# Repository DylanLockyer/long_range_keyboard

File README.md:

# long_range_keyboard
Creating a wireless keyboard with a range of 10km.

\*\*\* Not yet finished\*\*\*

The goal is to create a module which can be used for two purposes. One module can be connected over USB to a keyboard which will provide input to an STM32. The other circuit will be connected to a computer (in this case an Nvidia Jetson Nano) over usb. The STM32 on the second board will emulate an HID keyboard, and will relay the keystrokes from the keyboard which will be sent between the devices over LORA wireless communication. The board is in the PCB layout stage.

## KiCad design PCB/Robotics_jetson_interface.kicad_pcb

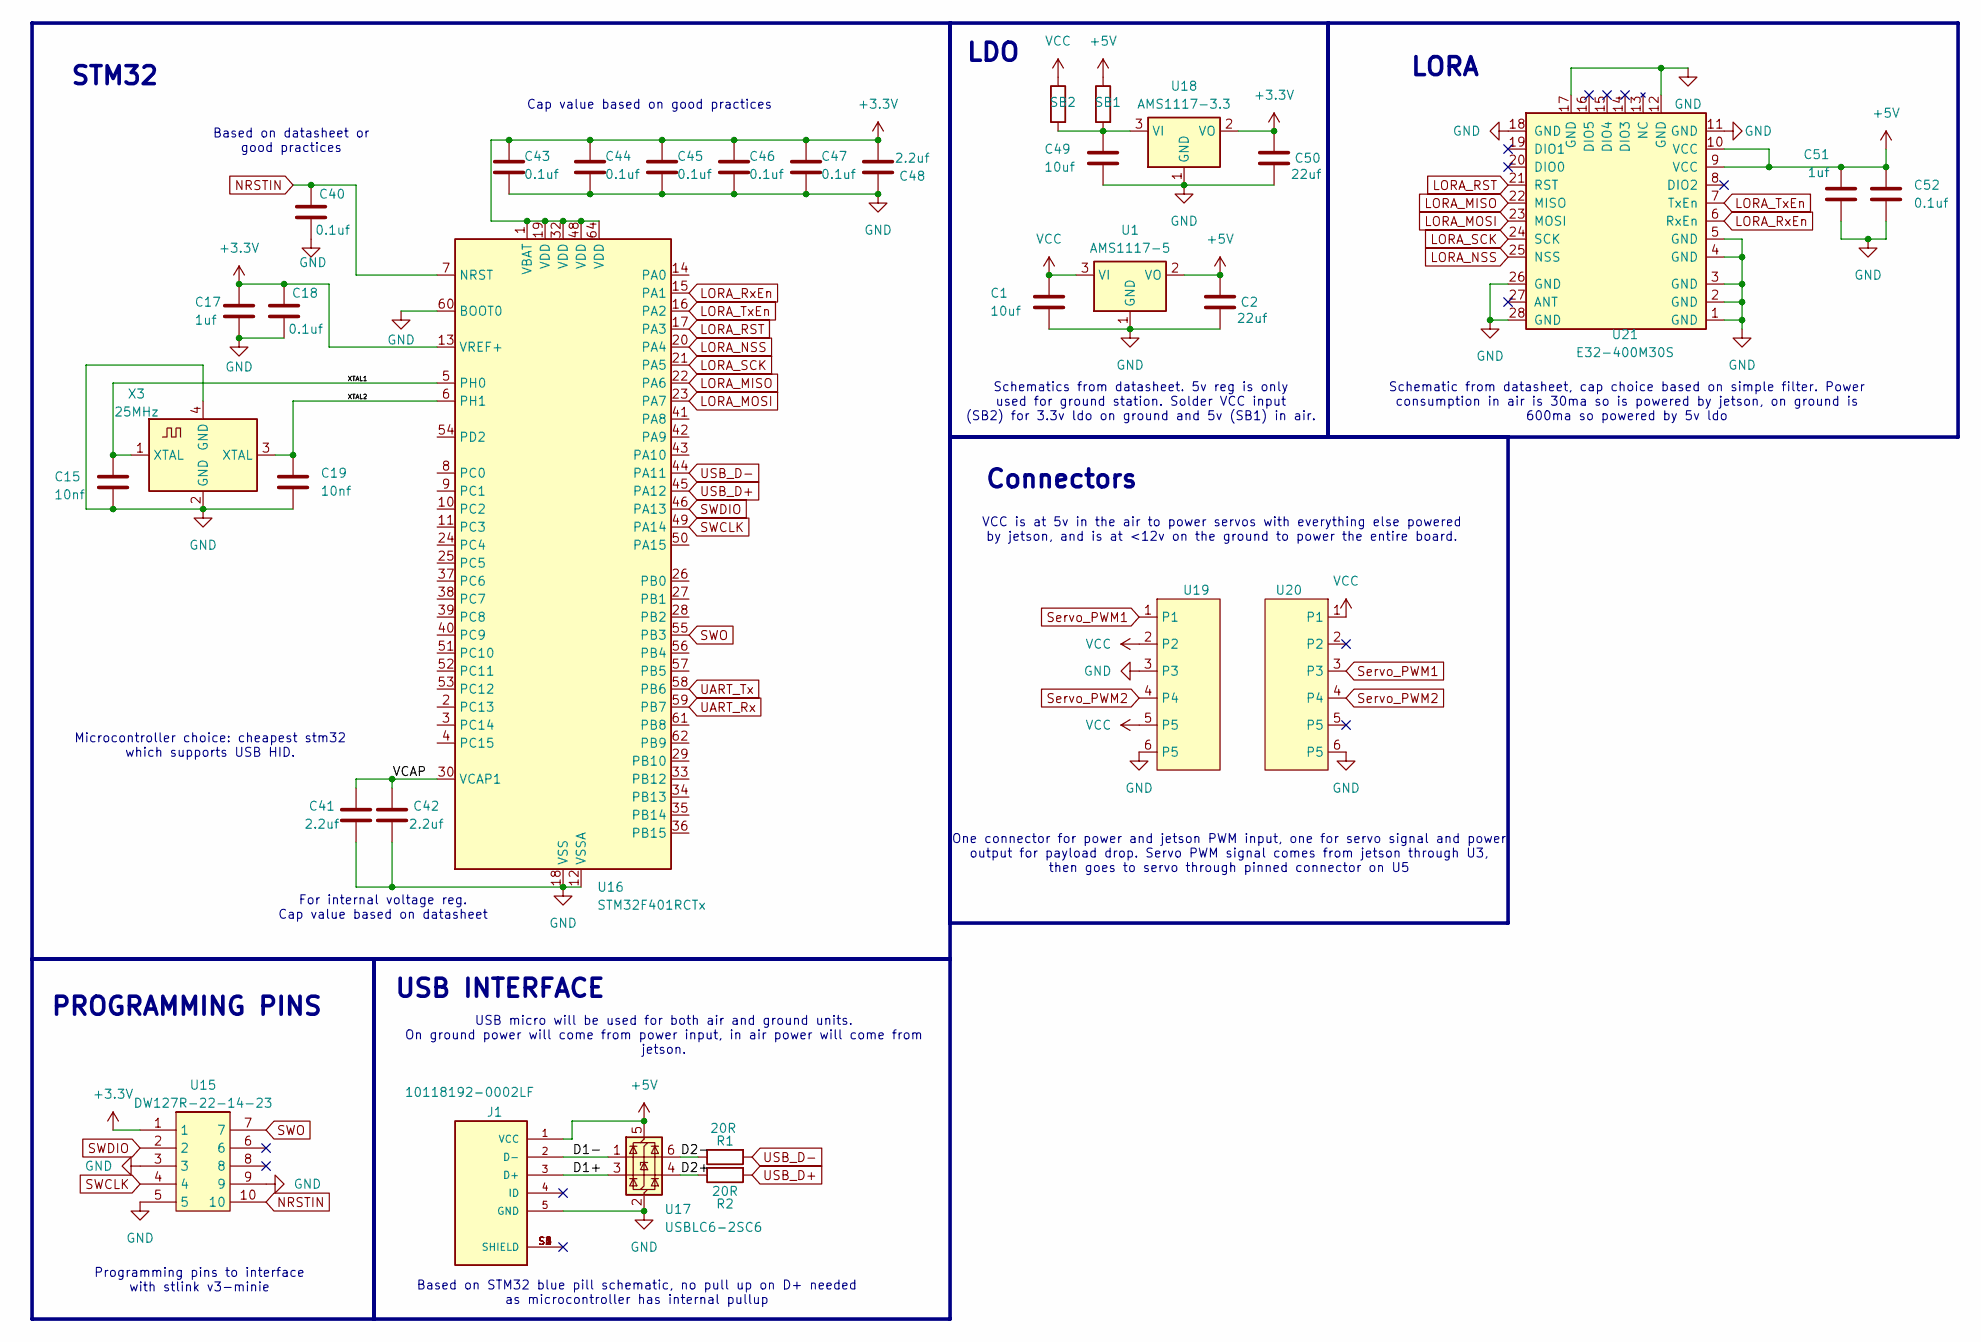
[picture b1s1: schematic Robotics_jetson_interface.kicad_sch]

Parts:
C1, C49: 10uf; C_0805_2012Metric
C2, C50: 22uf; C_0805_2012Metric_Pad1.18x1.45mm_HandSolder
C15, C19: 10nf; C_0805_2012Metric
C17, C51: 1uf; C_0603_1608Metric
C18, C40, C43, C44, C45, C46, C47, C52: 0.1uf; C_0402_1005Metric
C41, C42, C48: 2.2uf; C_0402_1005Metric
J1: 10118192-0002LF; AMPHENOL_10118192-0002LF; PARTREV B
R1, R2: 20R; R_0603_1608Metric
SB1, SB2: C_0603_1608Metric
U1: AMS1117-5; SOT-223-3_TabPin2
U15: DW127R-22-14-23
U16: STM32F401RCTx; LQFP-64_10x10mm_P0.5mm
U17: USBLC6-2SC6; SOT-23-6
U18: AMS1117-3.3; SOT-223-3_TabPin2
U19, U20: B06B-XASK-1-A
U21: E32-400M30S; E22-900M30S; PARTREV 1.4
X3: 25MHz; Crystal_SMD_3225-4Pin_3.2x2.5mm

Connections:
+3.3V: C17.1, C18.2, C43.1, C44.1, C45.1, C46.1, C47.1, C48.1, C50.1, U15.1, U16.1 (VBAT), U16.13 (VREF+), U16.19 (VDD), U16.32 (VDD), U16.48 (VDD), U16.64 (VDD), U18.2 (VO)
+5V: C2.1, C51.1, C52.1, J1.1 (VCC), SB1.1, U1.2 (VO), U17.5 (VBUS), U21.9 (VCC), U21.10 (VCC)
/D1+: J1.3 (D+), U17.3 (I/O2)
/D1-: J1.2 (D-), U17.1 (I/O1)
/D2+: R2.1, U17.4 (I/O2)
/D2-: R1.1, U17.6 (I/O1)
/VCAP: C41.2, C42.2, U16.30 (VCAP1)
/XTAL1: C15.1, U16.5 (PH0), X3.1 (XTAL)
/XTAL2: C19.1, U16.6 (PH1), X3.3 (XTAL)
GND: C1.2, C2.2, C15.2, C17.2, C18.1, C19.2, C40.1, C41.1, C42.1, C43.2, C44.2, C45.2, C46.2, C47.2, C48.2, C49.2, C50.2, C51.2, C52.2, J1.5 (GND), U1.1 (GND), U15.3, U15.5, U15.9, U16.12 (VSSA), U16.18 (VSS), U16.31 (VSS), U16.47 (VSS), U16.60 (BOOT0), U16.63 (VSS), U17.2 (GND), U18.1 (GND), U19.3, U19.6 (P5), U20.6 (P5), U21.1 (GND), U21.2 (GND), U21.3 (GND), U21.4 (GND), U21.5 (GND), U21.11 (GND), U21.12 (GND), U21.17 (GND), U21.18 (GND), U21.26 (GND), U21.28 (GND), X3.2 (GND), X3.4 (GND)
LORA_MISO: U16.22 (PA6), U21.22 (MISO)
LORA_MOSI: U16.23 (PA7), U21.23 (MOSI)
LORA_NSS: U16.20 (PA4), U21.25 (NSS)
LORA_RST: U16.17 (PA3), U21.21 (RST)
LORA_RxEn: U16.15 (PA1), U21.6 (RxEn)
LORA_SCK: U16.21 (PA5), U21.24 (SCK)
LORA_TxEn: U16.16 (PA2), U21.7 (TxEn)
NRSTIN: C40.2, U15.10, U16.7 (NRST)
unnamed: C49.1, SB1.2, SB2.2, U18.3 (VI)
SWCLK: U15.4, U16.49 (PA14)
SWDIO: U15.2, U16.46 (PA13)
SWO: U15.7, U16.55 (PB3)
Servo_PWM1: U19.1, U20.3
Servo_PWM2: U19.4, U20.4
UART_Rx: U16.59 (PB7)
UART_Tx: U16.58 (PB6)
USB_D+: R2.2, U16.45 (PA12)
USB_D-: R1.2, U16.44 (PA11)
VCC: C1.1, SB2.1, U1.3 (VI), U19.2, U19.5, U20.1

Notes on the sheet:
USB INTERFACE
Schematic from datasheet, cap choice based on simple filter. Power consumption in air is 30ma so is powered by jetson, on ground is 600ma so powered by 5v ldo
PROGRAMMING PINS
LORA
Schematics from datasheet. 5v reg is only used for ground station. Solder VCC input (SB2) for 3.3v ldo on ground and 5v (SB1) in air.
Based on datasheet or good practices
Based on STM32 blue pill schematic, no pull up on D+ needed as microcontroller has internal pullup
VCC is at 5v in the air to power servos with everything else powered by jetson, and is at <12v on the ground to power the entire board.
STM32
Microcontroller choice: cheapest stm32 which supports USB HID.
Connectors
For internal voltage reg. Cap value based on datasheet
One connector for power and jetson PWM input, one for servo signal and power output for payload drop. Servo PWM signal comes from jetson through U3, then goes to servo through pinned connector on U5
Cap value based on good practices
LDO
USB micro will be used for both air and ground units. On ground power will come from power input, in air power will come from jetson.
Programming pins to interface with stlink v3-minie

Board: 2 copper layers, 33 parts (22 on the bottom side), 27 nets, no tracks yet.

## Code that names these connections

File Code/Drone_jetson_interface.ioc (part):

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Mcu.Name=STM32F401R(B-C)Tx
Mcu.Package=LQFP64
Mcu.UserName=STM32F401RCTx
PA1.GPIOParameters=GPIO_Label
PA1.GPIO_Label=LORA_RxEn
PA1.Signal=GPIO_Output
PA10.Mode=OTG/Dual_Role_Device
PA10.Signal=USB_OTG_FS_ID
PA11.Mode=OTG/Dual_Role_Device
PA11.Signal=USB_OTG_FS_DM
PA12.Mode=OTG/Dual_Role_Device
PA12.Signal=USB_OTG_FS_DP
PA13.Mode=Trace_Asynchronous_SW
PA13.Signal=SYS_JTMS-SWDIO
PA14.Mode=Trace_Asynchronous_SW
PA14.Signal=SYS_JTCK-SWCLK
PA2.GPIOParameters=GPIO_Label
PA2.GPIO_Label=LORA_TxEn
PA2.Signal=GPIO_Output
PA3.GPIOParameters=GPIO_Label
PA3.GPIO_Label=LORA_RST
PA3.Signal=GPIO_Output
PA4.Mode=NSS_Signal_Hard_Output
PA4.Signal=SPI1_NSS
PA5.Mode=Full_Duplex_Master
PA5.Signal=SPI1_SCK
PA6.Mode=Full_Duplex_Master
PA6.Signal=SPI1_MISO
PA7.Mode=Full_Duplex_Master
PA7.Signal=SPI1_MOSI
PA9.Mode=Activate_VBUS
PA9.Signal=USB_OTG_FS_VBUS
PB3.Mode=Trace_Asynchronous_SW
PB3.Signal=SYS_JTDO-SWO
PC6.Signal=S_TIM3_CH1
PC7.Signal=S_TIM3_CH2
PC8.GPIOParameters=GPIO_Label
PC8.GPIO_Label=MOTOR_ERROR
PC8.Signal=GPIO_Input
PC9.GPIOParameters=GPIO_Label
PC9.GPIO_Label=MOTOR_SLEEP
PC9.Signal=GPIO_Output
PH0\ -\ OSC_IN.Mode=HSE-External-Oscillator
PH0\ -\ OSC_IN.Signal=RCC_OSC_IN
PH1\ -\ OSC_OUT.Mode=HSE-External-Oscillator
PH1\ -\ OSC_OUT.Signal=RCC_OSC_OUT
RCC.HSE_VALUE=25000000
RCC.SYSCLKFreq_VALUE=16000000
board=custom
